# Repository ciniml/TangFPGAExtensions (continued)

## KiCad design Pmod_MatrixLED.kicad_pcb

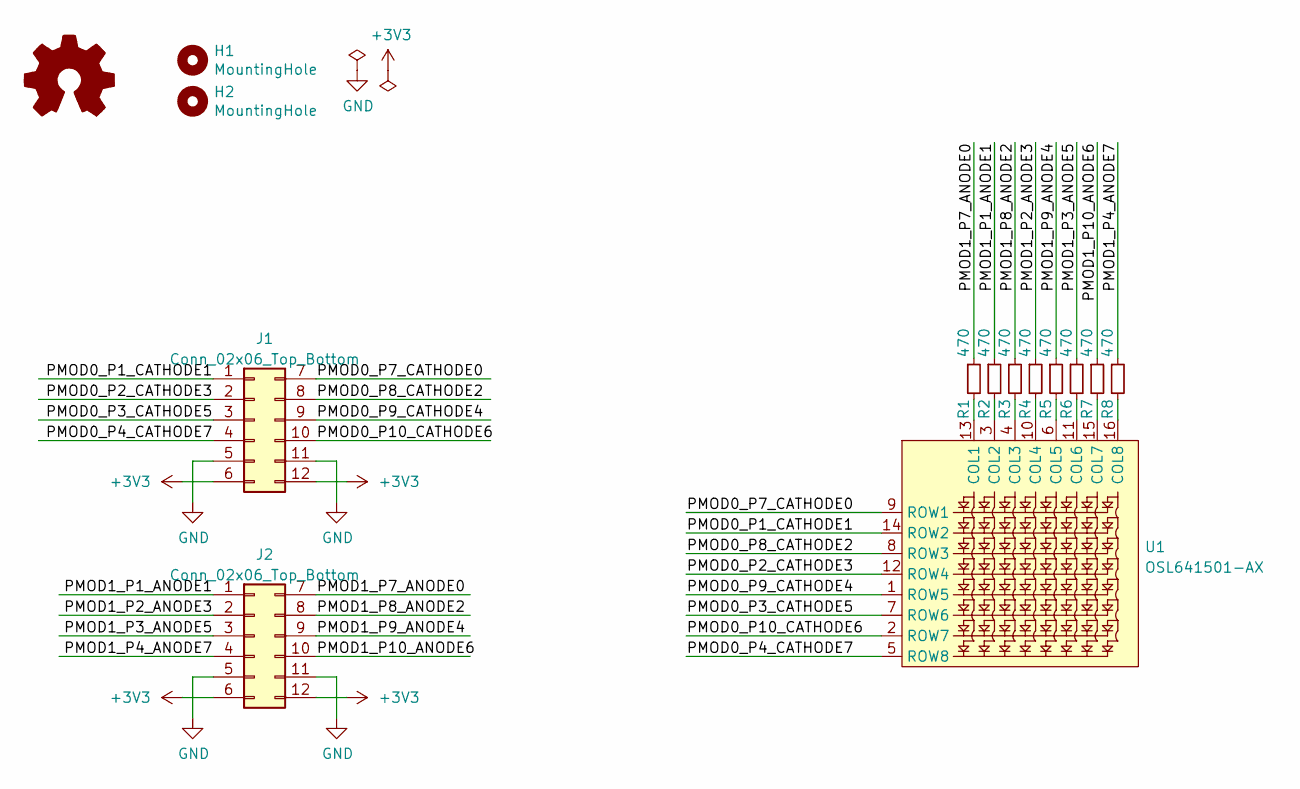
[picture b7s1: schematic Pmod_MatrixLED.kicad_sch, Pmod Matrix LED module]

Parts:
H1, H2: MountingHole; MountingHole_3.2mm_M3_Mask
J1, J2: Conn_02x06_Top_Bottom; Conn_Pmod_Spec_B_Thin
LOGO1: Logo_Open_Hardware_Small; logo
R1, R2, R3, R4, R5, R6, R7, R8: 470; R_Axial_DIN0204_L3.6mm_D1.6mm_P5.08mm_Horizontal_with_1608m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
U1: OSL641501-AX

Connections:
+3V3: J1.6, J1.12, J2.6, J2.12
/PMOD0_P1_CATHODE1: J1.1, U1.14 (ROW2)
/PMOD0_P2_CATHODE3: J1.2, U1.12 (ROW4)
/PMOD0_P3_CATHODE5: J1.3, U1.7 (ROW6)
/PMOD0_P4_CATHODE7: J1.4, U1.5 (ROW8)
/PMOD0_P7_CATHODE0: J1.7, U1.9 (ROW1)
/PMOD0_P8_CATHODE2: J1.8, U1.8 (ROW3)
/PMOD0_P9_CATHODE4: J1.9, U1.1 (ROW5)
/PMOD0_P10_CATHODE6: J1.10, U1.2 (ROW7)
/PMOD1_P1_ANODE1: J2.1, R2.1
/PMOD1_P2_ANODE3: J2.2, R4.1
/PMOD1_P3_ANODE5: J2.3, R6.1
/PMOD1_P4_ANODE7: J2.4, R8.1
/PMOD1_P7_ANODE0: J2.7, R1.1
/PMOD1_P8_ANODE2: J2.8, R3.1
/PMOD1_P9_ANODE4: J2.9, R5.1
/PMOD1_P10_ANODE6: J2.10, R7.1
GND: J1.5, J1.11, J2.5, J2.11
unnamed: R1.2, U1.13 (COL1)
unnamed: R2.2, U1.3 (COL2)
unnamed: R3.2, U1.4 (COL3)
unnamed: R4.2, U1.10 (COL4)
unnamed: R5.2, U1.6 (COL5)
unnamed: R6.2, U1.11 (COL6)
unnamed: R7.2, U1.15 (COL7)
unnamed: R8.2, U1.16 (COL8)

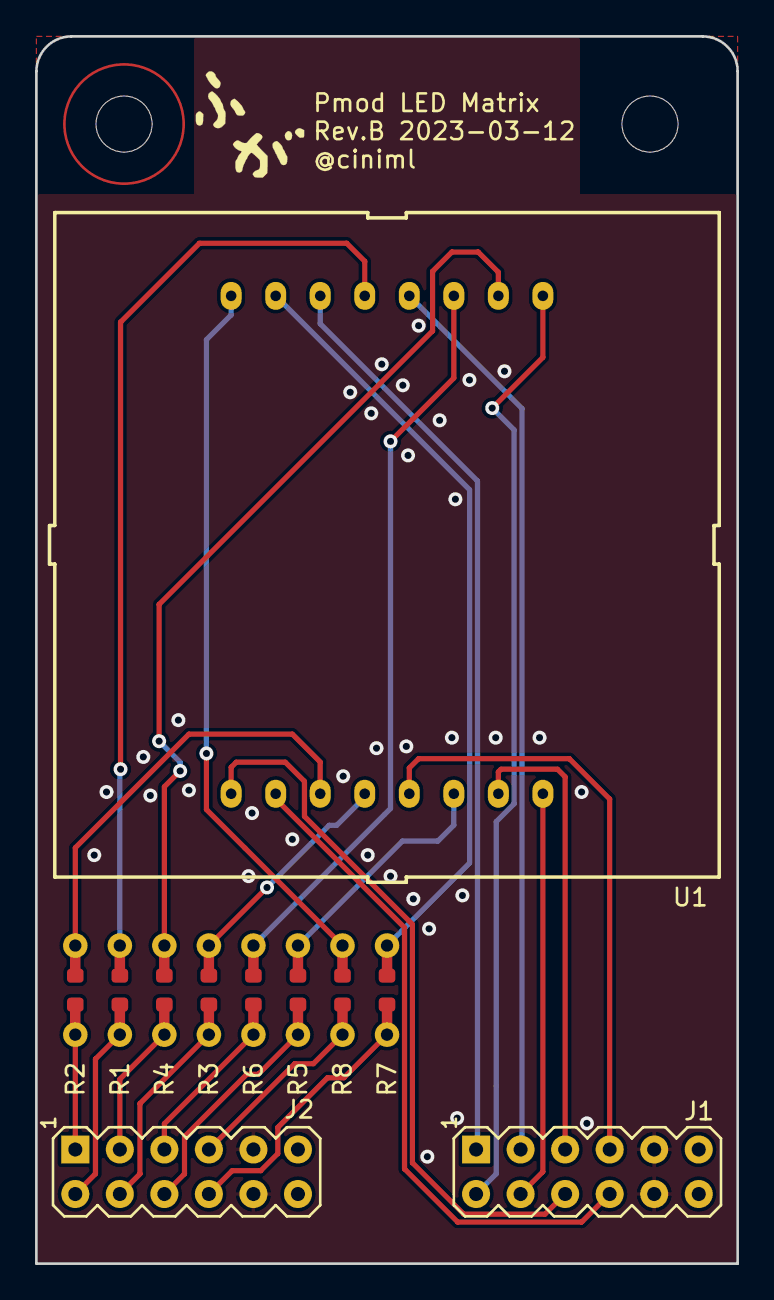
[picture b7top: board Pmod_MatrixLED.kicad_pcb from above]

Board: 2 copper layers, 40.0 x 70.0 mm, 14 parts (0 on the bottom side), 26 nets.

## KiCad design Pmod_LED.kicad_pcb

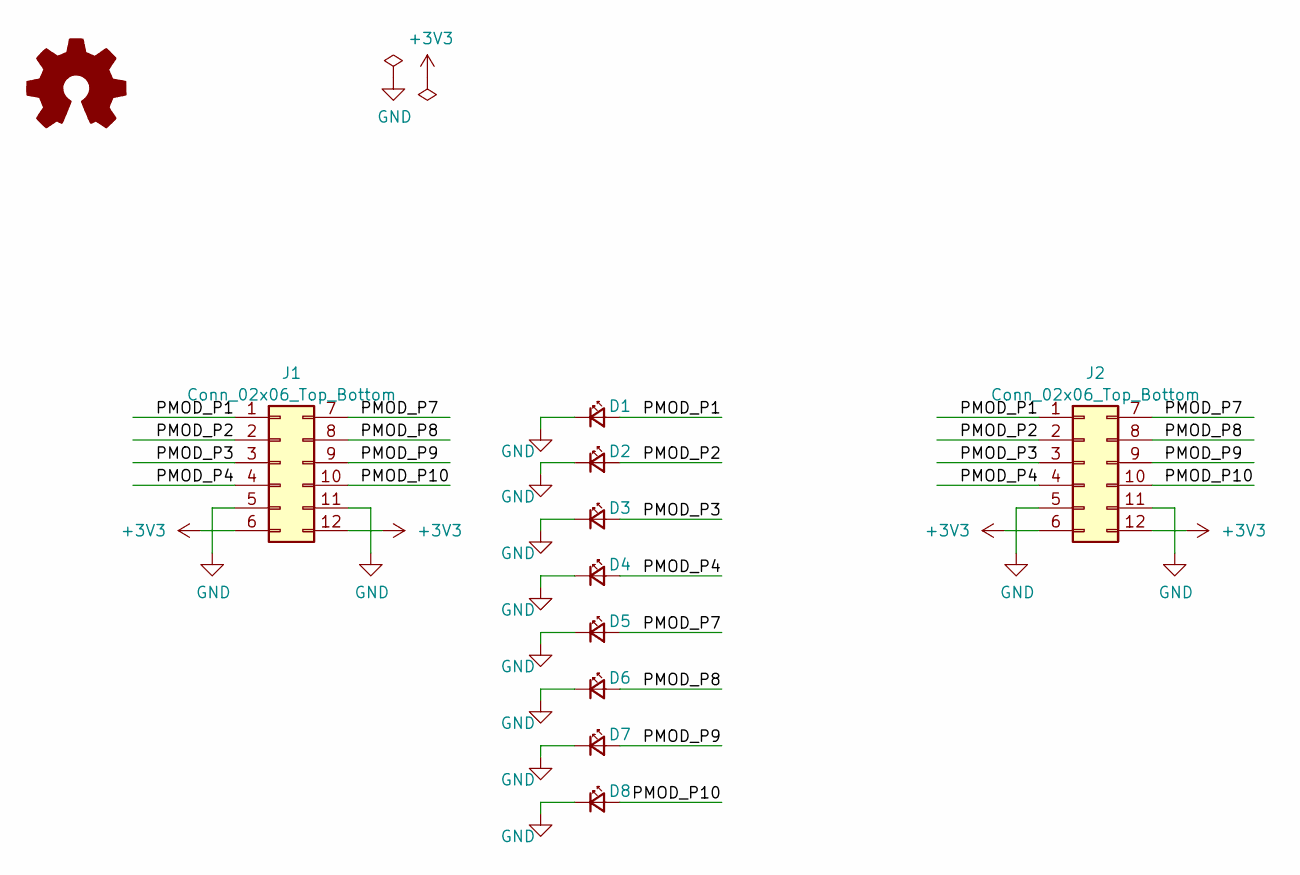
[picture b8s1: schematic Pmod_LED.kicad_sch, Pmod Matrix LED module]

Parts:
D1, D2, D3, D4, D5, D6, D7, D8: RED; LED_D3.0mm
J1: Conn_02x06_Top_Bottom; Conn_Pmod_Spec_B_Thin
J2: Conn_02x06_Top_Bottom; Conn_Pmod_Spec_D_Thin
LOGO1: Logo_Open_Hardware_Small; logo

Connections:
+3V3: J1.6, J1.12, J2.6, J2.12
/PMOD_P1: D1.2 (A), J1.1, J2.1
/PMOD_P2: D2.2 (A), J1.2, J2.2
/PMOD_P3: D3.2 (A), J1.3, J2.3
/PMOD_P4: D4.2 (A), J1.4, J2.4
/PMOD_P7: D5.2 (A), J1.7, J2.7
/PMOD_P8: D6.2 (A), J1.8, J2.8
/PMOD_P9: D7.2 (A), J1.9, J2.9
/PMOD_P10: D8.2 (A), J1.10, J2.10
GND: D1.1 (K), D2.1 (K), D3.1 (K), D4.1 (K), D5.1 (K), D6.1 (K), D7.1 (K), D8.1 (K), J1.5, J1.11, J2.5, J2.11

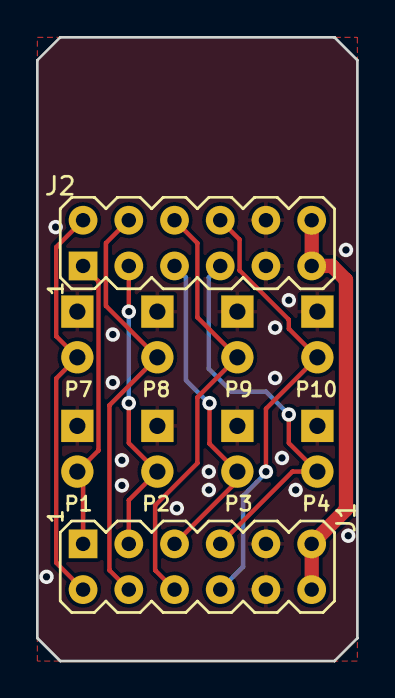
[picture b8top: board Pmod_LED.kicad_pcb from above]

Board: 2 copper layers, 17.8 x 34.6 mm, 11 parts (1 on the bottom side), 10 nets.

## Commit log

2023-04-01 Rev.B
2023-04-01 Add README
2023-04-02 Add schematic. Add TangPrimer20K extender doc.
2023-04-02 Add link to primer 20K extender.
2023-05-30 Add Pmod Multi Segment (Single Port) board design
2023-05-31 Add TangNano20K PmodBase description and update to Rev.B
2023-10-31 Add Pmod Debug baord description.
2024-03-17 ADd Pmod Ethernet Adapter
2024-03-17 Add Pmod DisplayPort
2024-03-17 Add assembly file
2024-03-17 Change DisplayPort receptacle to HOAUC HYC16-DP20-178
2024-07-31 Add akiduki list for Tang Nano 9K board
2024-08-02 Add Pmod Adapter Ethernet doc
